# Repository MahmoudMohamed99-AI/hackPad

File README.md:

# 🎹 Hackpad

A custom macropad designed and built as part of the **Hack Club Stardance Hackpad Mission**.

## 📖 About

Hackpad is a small custom keyboard/macropad designed to provide a set of programmable buttons for quickly performing common actions.

The project focuses on designing the hardware from scratch, creating the PCB, assembling the components, and programming the macropad.

## 🎯 Goals

* Design a custom macropad PCB
* Create a functional and compact keyboard
* Program each key to perform a specific action
* Learn the basics of PCB design and electronics
* Build and test the hardware myself

## 🛠️ Hardware

The project uses:

* Custom PCB
* Mechanical keyboard switches
* Keycaps
* Microcontroller
* Diodes
* USB connection
* Other required electronic components

## 💻 Software

The firmware will be responsible for:

* Detecting key presses
* Mapping keys to specific functions
* Sending keyboard commands to the computer

## 🔧 Design & Build Process

The project is being developed through the following stages:

1. 💡 **Idea** — Define the purpose and layout of the macropad.
2. 📐 **Schematic** — Design the electronic circuit.
3. 🧩 **PCB Design** — Create and route the custom PCB.
4. 🏭 **PCB Manufacturing** — Manufacture the designed PCB.
5. 🔨 **Assembly** — Solder and assemble the components.
6. 💻 **Firmware** — Program the macropad.
7. 🧪 **Testing** — Test every key and fix any hardware or software issues.
8. 🚀 **Final Build** — Complete and document the finished Hackpad.

## 📁 Project Structure

```text
Hackpad/
│
├── PCB/
│   ├── schematic/
│   ├── pcb/
│   └── gerbers/
│
├── Firmware/
│
├── CAD/
│
├── Documentation/
│
└── README.md
```

## 📸 Build Log

Photos, design files, testing results, and progress updates will be added to this repository as the project develops.

## 🌟 Stardance

This project is being built as part of **Hack Club Stardance** and the **Hackpad Mission**.

## 👤 Author

**Mahmoud Mohamed**

GitHub: [@MahmoudMohamed99-AI](https://github.com/MahmoudMohamed99-AI)

---

⭐ Built from scratch with curiosity, electronics, and a lot of soldering.

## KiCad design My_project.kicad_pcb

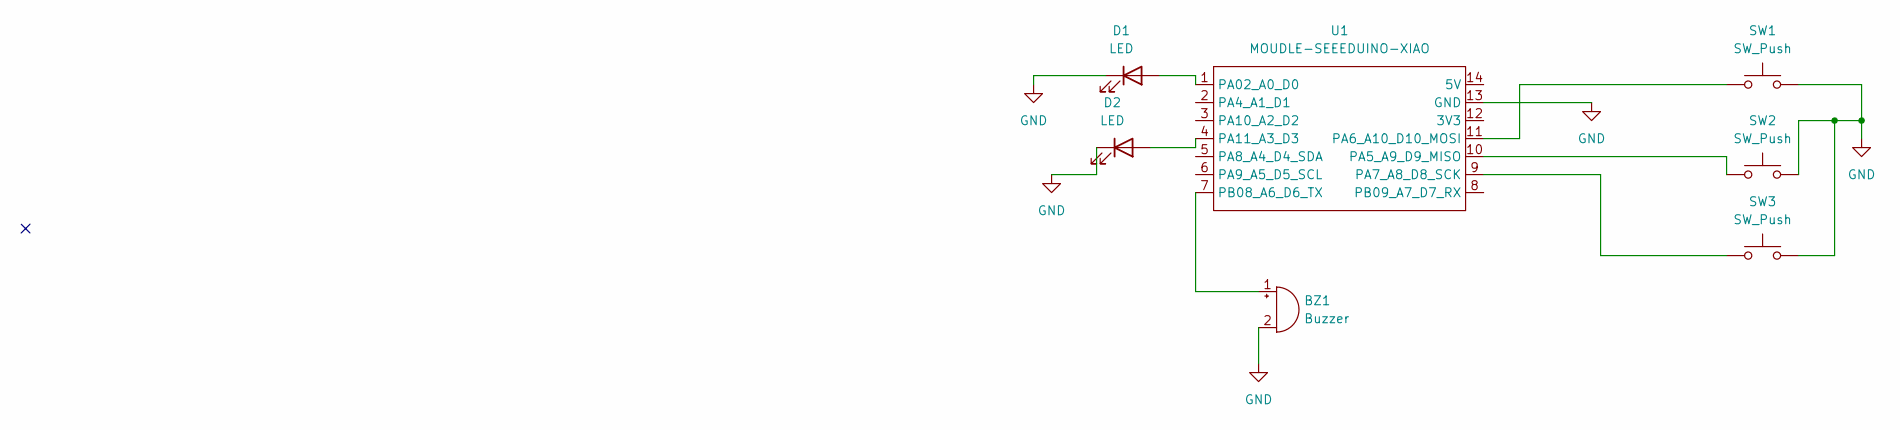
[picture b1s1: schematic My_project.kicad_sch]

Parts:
BZ1: Buzzer; Buzzer_12x9.5RM7.6
D1, D2: LED; LED_Cree-XHP50_3V_HighDensity
SW1, SW2, SW3: SW_Push; SW_Cherry_MX_1.00u_PCB
U1: MOUDLE-SEEEDUINO-XIAO; XIAO-Generic-Hybrid-14P-2.54-21X17.8MM

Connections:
GND: BZ1.2 (-), D1.1 (K), D2.1 (K), SW1.2, SW2.2, SW3.2, U1.13 (GND)
unnamed: BZ1.1 (+), U1.7 (PB08_A6_D6_TX)
unnamed: D1.2 (A), U1.1 (PA02_A0_D0)
unnamed: D2.2 (A), U1.4 (PA11_A3_D3)
unnamed: SW2.1, U1.10 (PA5_A9_D9_MISO)
unnamed: SW1.1, U1.11 (PA6_A10_D10_MOSI)
unnamed: SW3.1, U1.9 (PA7_A8_D8_SCK)

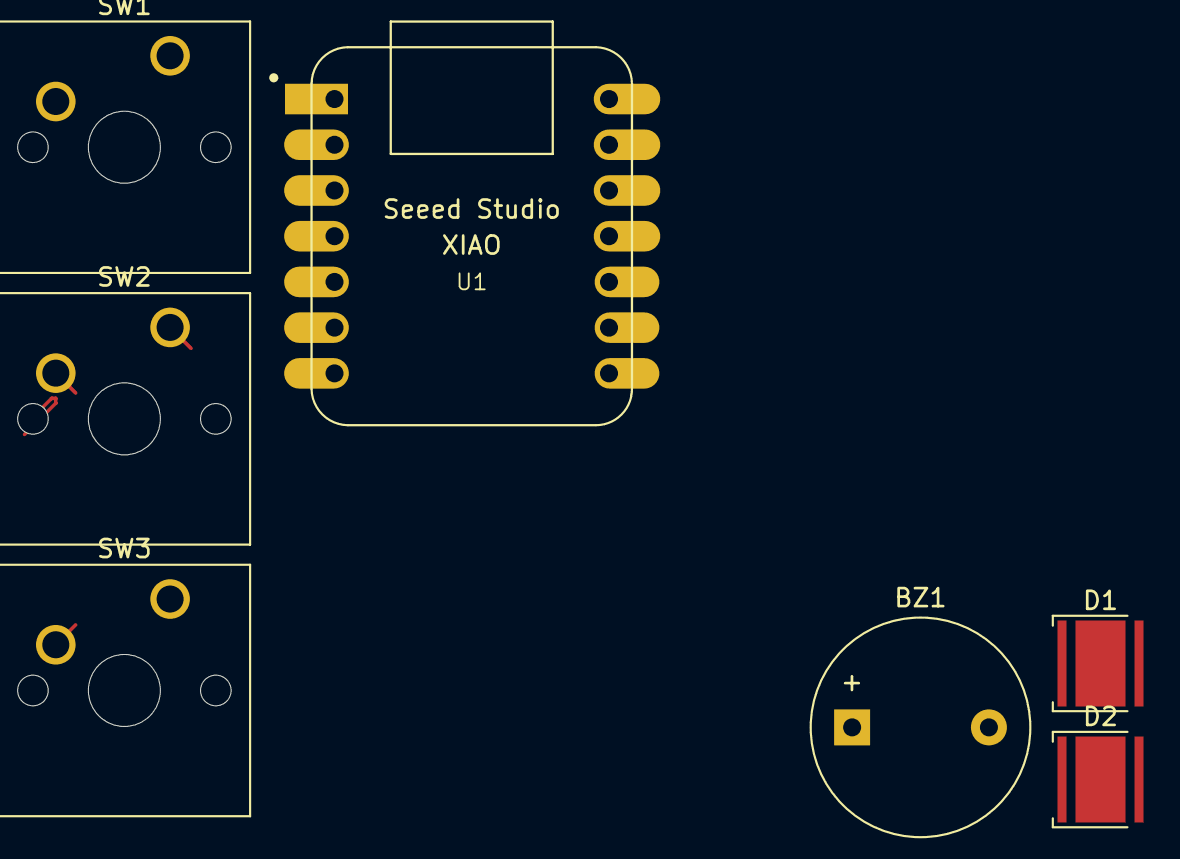
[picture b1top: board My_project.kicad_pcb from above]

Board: 2 copper layers, 7 parts (0 on the bottom side), 7 nets.
